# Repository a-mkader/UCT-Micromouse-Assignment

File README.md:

# EEE3088F Micromouse PCB-Assignment

A micromouse is, put very simply, a maze-solving robot. In this project, we will build a micromouse, focusing on the hardware of the robot, namely the power and sensing subsystems. <br /> <br />

## Motherboard Subsystem 
Fortunately, the motherboard subsystem has been designed for us. The motherboard houses the processor that will be the brain of the micromouse. <br />
<br />
<br />

## Power Subsystem
This subsystem will be required to drive the two motors of the micromouse while being responsible for charging the battery that will supply the micromouse as well.
### Requirements:
- Provide a minimum of 400mA to drive two motors (200mA per motor)
* Charge the battery
  * Sense the battery's state of charge
+ Switch ON/OFF
- Be able to plug into the motherboard
* Be an appropriate size for the robot <br />

A more detailed description of these requirements, as well as the pinouts for this subsystem, are listed [here](EEE3088F_2024_project_description_v11.pdf) on page 7.

## Sensing Subsystem
This subsystem will act as the robot's eyes. It will have to determine whether or not there is an obstruction in the way of the robot, and then send this information to the processor to take necessary action.
### Requirements:
* Object detection 
  * Reliable way of communicating this information to the processor
* Power saving by means of switching
+ Be able to plug into the motherboard
- Needs to be an appropriate size for the robot
  
Once again, a more detailed description of what exactly this module needs to do as well as its pinouts, can be found [here](EEE3088F_2024_project_description_v11.pdf) on page 9.

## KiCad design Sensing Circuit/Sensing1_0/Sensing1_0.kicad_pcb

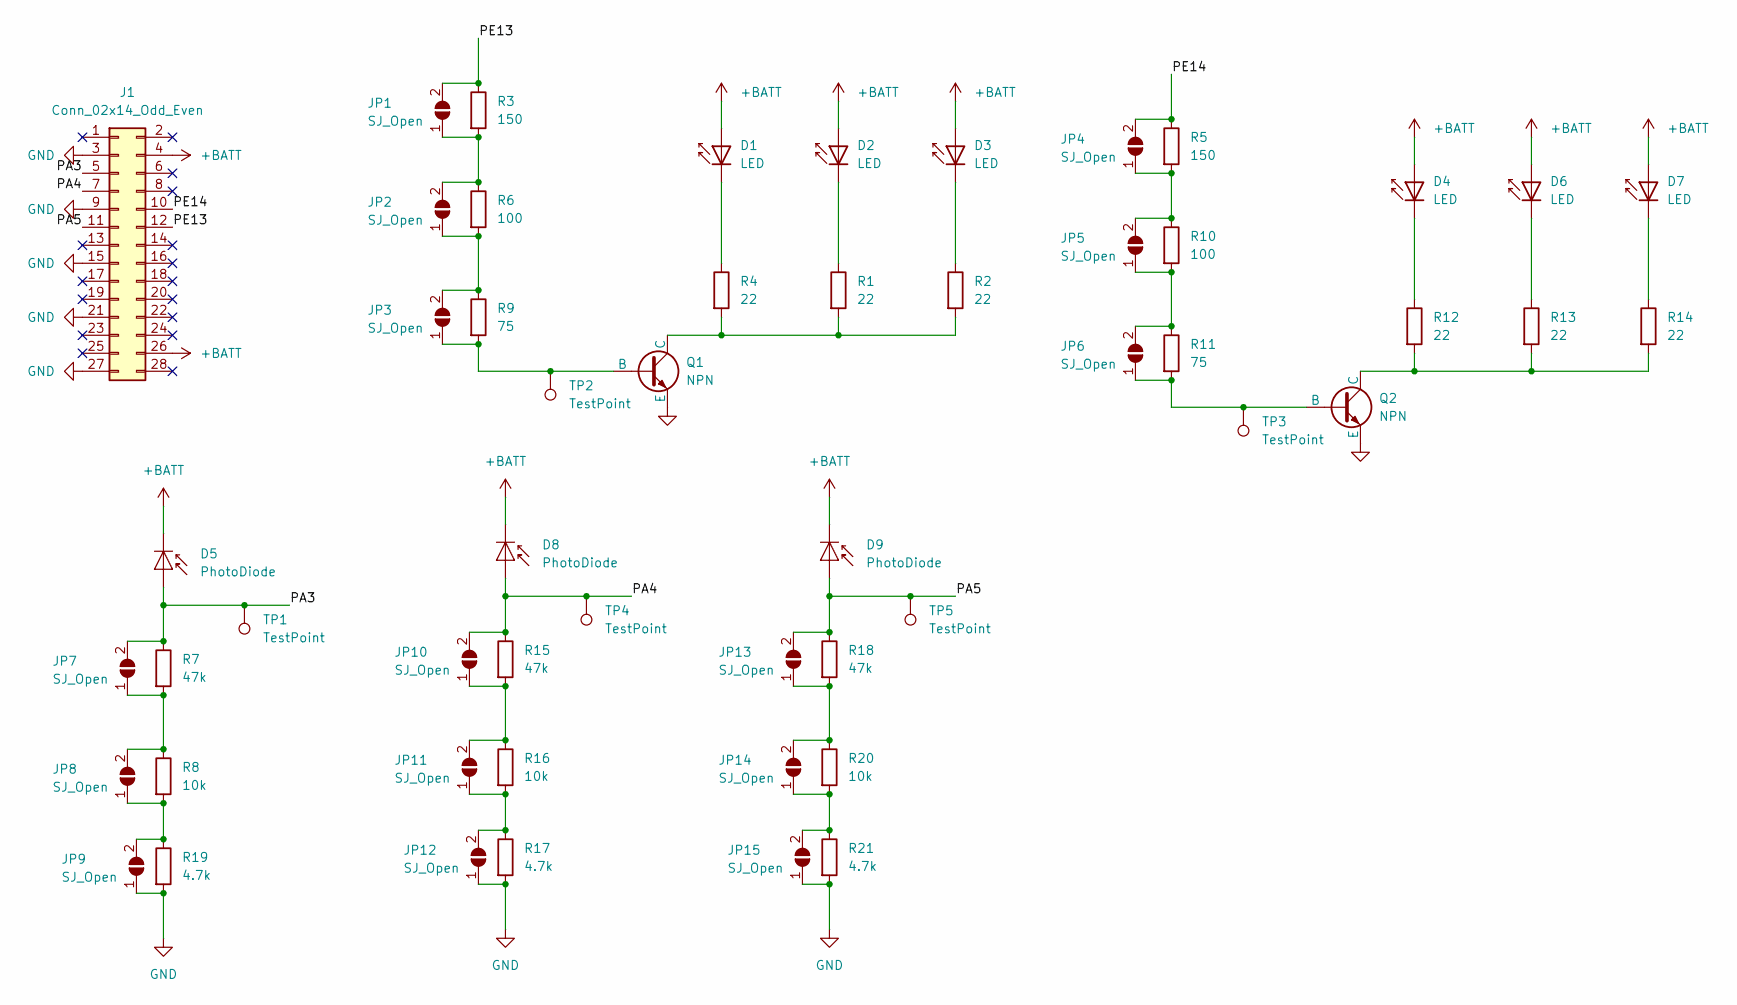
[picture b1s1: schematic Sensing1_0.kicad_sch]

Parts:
D1, D2, D3, D4, D6, D7: LED; LED_D5.0mm_Horizontal_O1.27mm_Z15.0mm; LCSC C55528
D5, D8, D9: PhotoDiode; LED_D5.0mm_Horizontal_O1.27mm_Z15.0mm; LCSC C2900211
J1: Conn_02x14_Odd_Even; PinSocket_2x14_P2.54mm_Vertical
JP1, JP2, JP3, JP4, JP5, JP6, JP7, JP8, JP9, JP10, JP11, JP12, JP13, JP14, JP15: SJ_Open; SolderJumper-2_P1.3mm_Open_RoundedPad1.0x1.5mm
Q1, Q2: NPN; SOT-23; LCSC C2145
R1, R2, R4, R12, R13, R14: 22; R_0603_1608Metric; LCSC C23345
R3, R5: 150; R_0603_1608Metric; LCSC C22808
R6, R10: 100; R_0603_1608Metric; LCSC C22775
R7, R15, R18: 47k; R_0603_1608Metric; LCSC C25819
R8, R16, R20: 10k; R_0603_1608Metric; LCSC C25804
R9, R11: 75; R_0603_1608Metric; LCSC C4275
R17, R19, R21: 4.7k; R_0603_1608Metric; LCSC C23162
TP1, TP2, TP3, TP4, TP5: TestPoint; TestPoint_Pad_1.5x1.5mm

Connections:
+BATT: D1.2 (A), D2.2 (A), D3.2 (A), D4.2 (A), D5.1 (K), D6.2 (A), D7.2 (A), D8.1 (K), D9.1 (K), J1.4, J1.26
/PA3: D5.2 (A), J1.5, JP7.2 (B), R7.1, TP1.1
/PA4: D8.2 (A), J1.7, JP10.2 (B), R15.1, TP4.1
/PA5: D9.2 (A), J1.11, JP13.2 (B), R18.1, TP5.1
/PE13: J1.12, JP1.2 (B), R3.1
/PE14: J1.10, JP4.2 (B), R5.1
GND: J1.3, J1.9, J1.15, J1.21, J1.27, JP9.1 (A), JP12.1 (A), JP15.1 (A), Q1.3 (E), Q2.3 (E), R17.2, R19.2, R21.2
unnamed: D1.1 (K), R4.1
unnamed: D2.1 (K), R1.1
unnamed: D3.1 (K), R2.1
unnamed: D4.1 (K), R12.1
unnamed: D6.1 (K), R13.1
unnamed: D7.1 (K), R14.1
unnamed: JP1.1 (A), JP2.2 (B), R3.2, R6.1
unnamed: JP2.1 (A), JP3.2 (B), R6.2, R9.1
unnamed: JP3.1 (A), Q1.2 (B), R9.2, TP2.1
unnamed: JP4.1 (A), JP5.2 (B), R5.2, R10.1
unnamed: JP5.1 (A), JP6.2 (B), R10.2, R11.1
unnamed: JP6.1 (A), Q2.2 (B), R11.2, TP3.1
unnamed: JP7.1 (A), JP8.2 (B), R7.2, R8.1
unnamed: JP8.1 (A), JP9.2 (B), R8.2, R19.1
unnamed: JP10.1 (A), JP11.2 (B), R15.2, R16.1
unnamed: JP11.1 (A), JP12.2 (B), R16.2, R17.1
unnamed: JP13.1 (A), JP14.2 (B), R18.2, R20.1
unnamed: JP14.1 (A), JP15.2 (B), R20.2, R21.1
unnamed: Q1.1 (C), R1.2, R2.2, R4.2
unnamed: Q2.1 (C), R12.2, R13.2, R14.2

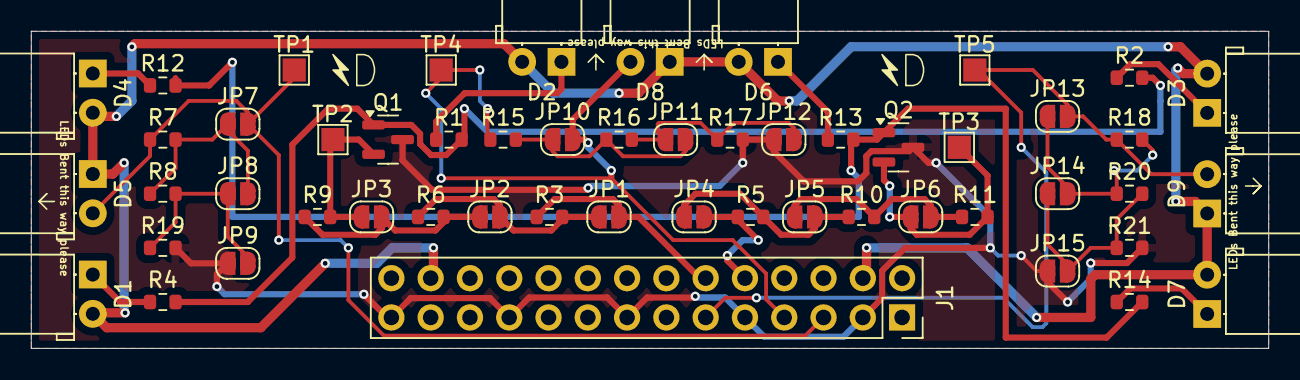
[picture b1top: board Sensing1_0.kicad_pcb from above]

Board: 2 copper layers, 80.0 x 20.5 mm, 53 parts (0 on the bottom side), 27 nets.

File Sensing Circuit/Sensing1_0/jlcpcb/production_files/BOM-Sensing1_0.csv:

Comment,Designator,Footprint,LCSC
NPN,"Q1,Q2",SOT-23,C2145
150,"R3,R5",R_0603_1608Metric,C22808
10k,"R16,R20,R8",R_0603_1608Metric,C25804
47k,"R15,R18,R7",R_0603_1608Metric,C25819
PhotoDiode,"D5,D8,D9",LED_D5.0mm_Horizontal_O1.27mm_Z15.0mm,C2900211
75,"R11,R9",R_0603_1608Metric,C4275
LED,"D1,D2,D3,D4,D6,D7",LED_D5.0mm_Horizontal_O1.27mm_Z15.0mm,C55528
TestPoint,TP5,TestPoint_Pad_1.5x1.5mm,
TestPoint,TP4,TestPoint_Pad_1.5x1.5mm,
TestPoint,TP3,TestPoint_Pad_1.5x1.5mm,
TestPoint,TP2,TestPoint_Pad_1.5x1.5mm,
TestPoint,TP1,TestPoint_Pad_1.5x1.5mm,
4.7k,R21,R_0603_1608Metric,
4.7k,R19,R_0603_1608Metric,
4.7k,R17,R_0603_1608Metric,
22,R14,R_0603_1608Metric,
22,R13,R_0603_1608Metric,
22,R12,R_0603_1608Metric,
100,R10,R_0603_1608Metric,
100,R6,R_0603_1608Metric,
22,R4,R_0603_1608Metric,
22,R2,R_0603_1608Metric,
22,R1,R_0603_1608Metric,
SJ_Open,JP15,SolderJumper-2_P1.3mm_Open_RoundedPad1.0x1.5mm,
SJ_Open,JP14,SolderJumper-2_P1.3mm_Open_RoundedPad1.0x1.5mm,
SJ_Open,JP13,SolderJumper-2_P1.3mm_Open_RoundedPad1.0x1.5mm,
SJ_Open,JP12,SolderJumper-2_P1.3mm_Open_RoundedPad1.0x1.5mm,
SJ_Open,JP11,SolderJumper-2_P1.3mm_Open_RoundedPad1.0x1.5mm,
SJ_Open,JP10,SolderJumper-2_P1.3mm_Open_RoundedPad1.0x1.5mm,
SJ_Open,JP9,SolderJumper-2_P1.3mm_Open_RoundedPad1.0x1.5mm,
SJ_Open,JP8,SolderJumper-2_P1.3mm_Open_RoundedPad1.0x1.5mm,
SJ_Open,JP7,SolderJumper-2_P1.3mm_Open_RoundedPad1.0x1.5mm,
SJ_Open,JP6,SolderJumper-2_P1.3mm_Open_RoundedPad1.0x1.5mm,
SJ_Open,JP5,SolderJumper-2_P1.3mm_Open_RoundedPad1.0x1.5mm,
SJ_Open,JP4,SolderJumper-2_P1.3mm_Open_RoundedPad1.0x1.5mm,
SJ_Open,JP3,SolderJumper-2_P1.3mm_Open_RoundedPad1.0x1.5mm,
SJ_Open,JP2,SolderJumper-2_P1.3mm_Open_RoundedPad1.0x1.5mm,
SJ_Open,JP1,SolderJumper-2_P1.3mm_Open_RoundedPad1.0x1.5mm,

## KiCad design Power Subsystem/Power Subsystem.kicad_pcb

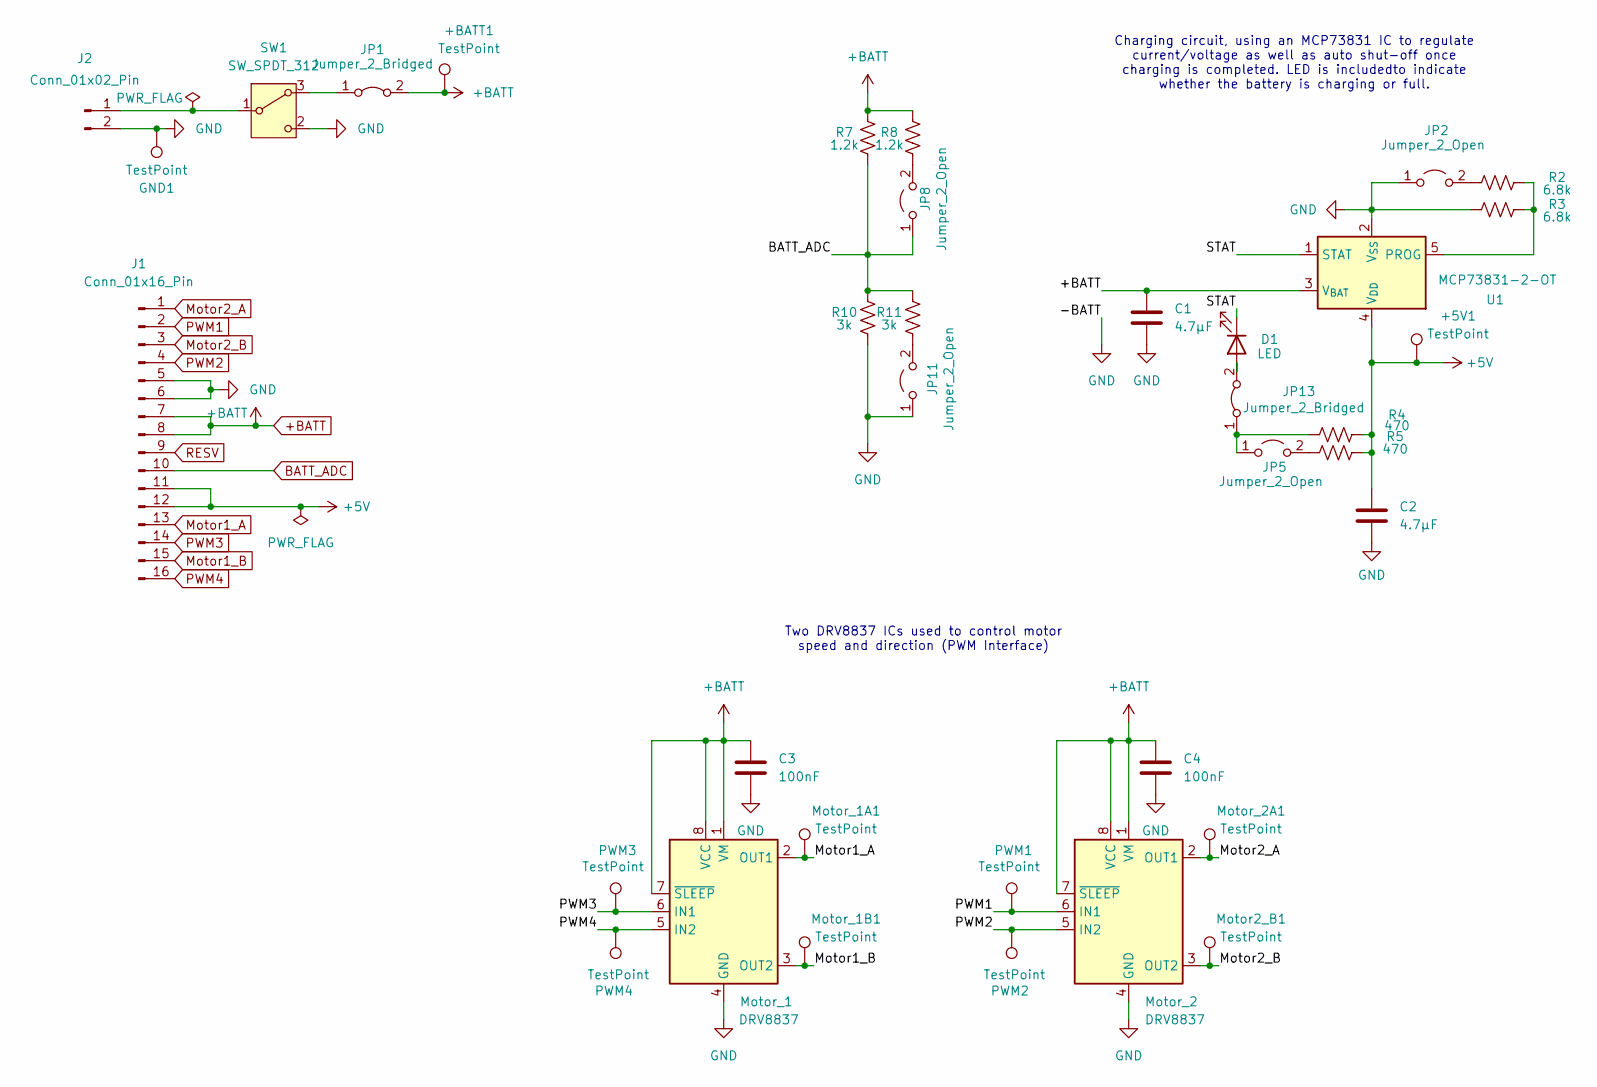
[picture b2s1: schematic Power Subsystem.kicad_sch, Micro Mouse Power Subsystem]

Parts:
+5V1: TestPoint; TestPoint_Keystone_5019_Minature
+BATT1: TestPoint; TestPoint_Keystone_5019_Minature
C1, C2: 4.7µF; C_0402_1005Metric; LCSC C1538
C3, C4: 100nF; C_0402_1005Metric; LCSC C1525
D1: LED; LED_0603_1608Metric; LCSC C2286
GND1: TestPoint; TestPoint_Keystone_5019_Minature
J1: Conn_01x16_Pin; PinHeader_2x08_P2.54mm_Vertical
J2: Conn_01x02_Pin; JST_PH_S2B-PH-K_1x02_P2.00mm_Horizontal
JP1, JP13: Jumper_2_Bridged; SolderJumper-2_P1.3mm_Bridged2Bar_RoundedPad1.0x1.5mm
JP2, JP5, JP8, JP11: Jumper_2_Open; SolderJumper-2_P1.3mm_Open_TrianglePad1.0x1.5mm
Motor2_B1: TestPoint; TestPoint_Keystone_5019_Minature
Motor_1, Motor_2: DRV8837; WSON-8-1EP_2x2mm_P0.5mm_EP0.9x1.6mm; LCSC C191000
Motor_1A1, Motor_1B1, Motor_2A1: TestPoint; TestPoint_Keystone_5019_Minature
PWM1, PWM2, PWM3, PWM4: TestPoint; TestPoint_Keystone_5019_Minature
R2, R3: 6.8k; R_0603_1608Metric; LCSC C23212
R4, R5: 470; R_0402_1005Metric; LCSC C25117
R7, R8: 1.2k; R_0603_1608Metric; LCSC C22765
R10, R11: 3k; R_0603_1608Metric; LCSC C4211
SW1: SW_SPDT_312; SW-TH_SS-12D10L5; LCSC C319012
U1: MCP73831-2-OT; SOT-23-5; LCSC C424093

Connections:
+5V: +5V1.1, C2.1, J1.11, J1.12, R4.2, R5.2, U1.4 (V_{DD})
/STAT: D1.1 (K), U1.1 (STAT)
BATT_ADC: J1.10, JP8.1 (A), R7.1, R10.2, R11.2
GND: C1.2, C2.2, C3.2, C4.2, GND1.1, J1.5, J1.6, J2.2, JP2.1 (A), JP11.1 (A), Motor_1.4 (GND), Motor_1.9 (GND), Motor_2.4 (GND), Motor_2.9 (GND), R3.1, R10.1, SW1.2 (C), U1.2 (V_{SS})
Motor1_A: J1.13, Motor_1.2 (OUT1), Motor_1A1.1
Motor1_B: J1.15, Motor_1.3 (OUT2), Motor_1B1.1
Motor2_A: J1.1, Motor_2.2 (OUT1), Motor_2A1.1
Motor2_B: J1.3, Motor2_B1.1, Motor_2.3 (OUT2)
unnamed: D1.2 (A), JP13.2 (B)
unnamed: J2.1, SW1.1 (B)
unnamed: JP2.2 (B), R2.1
unnamed: JP5.2 (B), R5.1
unnamed: JP8.2 (B), R8.1
unnamed: JP11.2 (B), R11.1
unnamed: JP5.1 (A), JP13.1 (A), R4.1
unnamed: R2.2, R3.2, U1.5 (PROG)
PWM1: J1.2, Motor_2.6 (IN1), PWM1.1
PWM2: J1.4, Motor_2.5 (IN2), PWM2.1
PWM3: J1.14, Motor_1.6 (IN1), PWM3.1
PWM4: J1.16, Motor_1.5 (IN2), PWM4.1
RESV: J1.9

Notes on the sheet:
Charging circuit, using an MCP73831 IC to regulate current/voltage as well as auto shut-off once charging is completed. LED is includedto indicate whether the battery is charging or full.
Two DRV8837 ICs used to control motor speed and direction (PWM Interface)

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
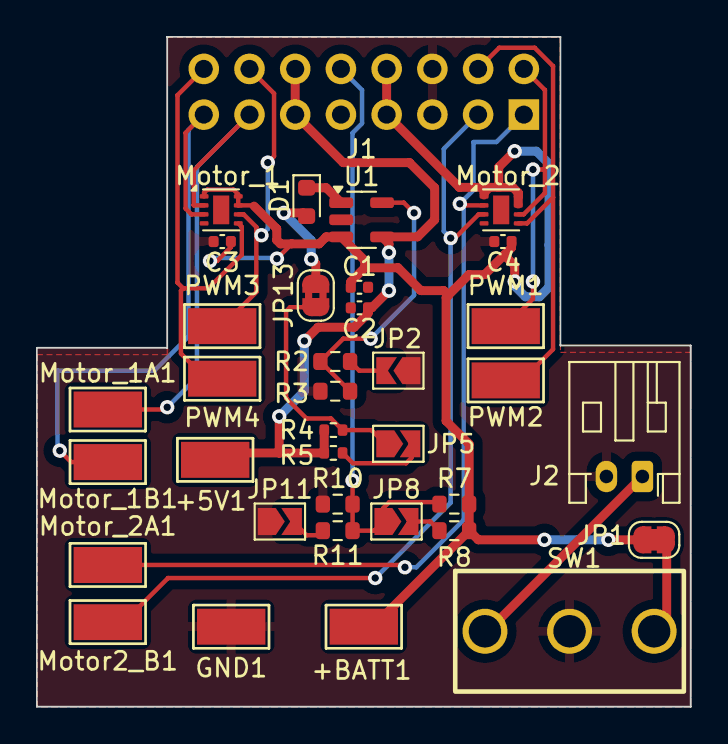
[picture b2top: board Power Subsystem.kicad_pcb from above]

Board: 2 copper layers, 36.3 x 37.2 mm, 36 parts (1 on the bottom side), 21 nets.

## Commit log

2024-03-14 Added folder with KiCAD files
2024-03-16 Project brief v4
2024-03-16 Charging circuit updated, connections to pin headers not complete
2024-03-17 Create Sensing Subsystem
2024-03-17 Final design (2 errors, 3 warnings)
2024-03-17 Schematic Version 1 (2 errors, 3 warnings)
2024-03-18 PCB design started, few connections missing
2024-03-24 Sensing Circuit KiCad files added
2024-03-24 Most recent Schematic/PCB
2024-03-24 Sensing Circuit KiCaD files updated
2024-03-24 Final Schematic and PCB designs
2024-03-24 Latest project brief
2024-03-24 Screenshots for submission
2024-04-09 Added .gitignore file
2024-04-09 Removed old versions of project brief
2024-04-09 Removed redundant directories/files
2024-04-09 Folder containing datasheets consulted during design
2024-04-09 Added untracked files
2024-04-17 Latest version of project brief
2024-04-17 Datasheets folders updated
2024-04-20 Datasheet for switch
2024-04-20 Removed all files, in order to reupload neater
2024-04-20 Folder for all KiCad files created
2024-04-20 Datasheets folder updated
2024-04-21 Sensig circuit schematic files updated, Datasheets added, Schematic and PCB figures added and interim report added.
2024-09-09 Moved EEE3088F files, added EEE3099S files
2024-09-14 Motors working (right moving twice as fast as left - will have to debug)
2024-09-14 Motor speed updated. Still some issues
2024-09-14 IR LED Patterns added.
2024-09-16 Branch 'abdul' created
2024-09-16 Finalising merge
2024-09-16 Added switch functionality for motors. Left/Right issue still persists
2024-09-16 Motor logic working, IR readings still tweaking out. Motor reverse also bugged, need to compate with the template.
2024-09-17 Changed patterns IRLEDs to just down
2024-09-17 Motor logic fully operational. Reverse is still an issue.
2024-09-17 Merging with main
2024-09-17 Motor test code
2024-09-17 Motor code more efficient.
2024-09-18 Changed alot. getting there though
2024-09-18 This should be working for milestone 2 Just needs to be calibrated in the maze.
2024-09-19 Readyyyy for Demoooooooooo!!!!!!!!!!!!!!!!1
2024-09-19 Demo passed 100%
2024-09-23 Micromouse Infopack Uploaded
2024-09-23 Reports folder added
2024-09-23 Changes made for Milestone 2 Report
2024-10-16 Maze solving algo/sim
2024-10-16 Optimisation code added/changed
2024-10-17 After night shift code
2024-10-17 New calibration logic
2024-10-22 The final code. Didnt quite work but the irght idea was there. :(
2024-10-22 Gitignore added
